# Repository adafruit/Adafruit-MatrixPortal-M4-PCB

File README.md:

## Adafruit MatrixPortal M4 - CircuitPython Powered Internet Display PCB

<a href="http://www.adafruit.com/products/4745"><br/>
Click here to purchase one from the Adafruit shop</a>

PCB files for the Adafruit MatrixPortal M4 - CircuitPython Powered Internet Display. 

Format is EagleCAD schematic and board layout
* https://www.adafruit.com/product/4745

### Description

Folks love our [wide selection of RGB matrices](https://www.adafruit.com/category/327) and accessories, for making custom colorful LED displays... and our RGB Matrix Shields and FeatherWings can be quickly soldered together to make the wiring much easier. But what if we made it even easier than that? **Like, no solder, no wiring, just instant plug-and-play?** Dream no more - with the **Adafruit Matrix Portal add-on for RGB Matrices**, there's never been an easier way to create powerful Internet-connected LED displays.

Plug directly into the back of [any HUB-75 compatible display (all the ones we stock will work) from 16x32 up to 64x64](https://www.adafruit.com/category/327)! Use the included screws to attach the power cable to the power plugs with a common screwdriver, then power it with any USB C power supply. (For larger projects, power the matrices with a separate 5V power adapter)

Then code up your project in [CircuitPython](https://learn.adafruit.com/rgb-led-matrices-matrix-panels-with-circuitpython) or [Arduino](https://learn.adafruit.com/adafruit-protomatter-rgb-matrix-library), our Protomatter matrix library works great on the SAMD51 chipset, knowing that you've got the wiring and level shifting all handled. Here's what you get:

 * **ATSAMD51J19 Cortex M4 processor**, 512KB flash, 192K of SRAM, with full Arduino or CircuitPython support
 * **ESP32 WiFi co-processor** with TLS support and SPI interface to the M4, with full Arduino or CircuitPython support
 * **USB Type C** connector for data and power connectivity
 * [**I2C STEMMA QT connector** for plug-n-play use of any of our STEMMA QT devices or sensors](https://www.adafruit.com/category/620) can also be used with [any Grove I2C devices using this adapter cable](https://www.adafruit.com/product/4528))
 * **JST 3-pin connector** that also has analog input/output, say for adding audio playback to projects
 * **LIS3DH accelerometer** for digital sand projects or detecting taps/orientation.
 * **GPIO breakouts** including 4 analog outputs with PWM and SPI support for adding other hardware.
 * **Address E line jumper** for use with 64x64 matrices (check your matrix to see which pin is used for address E!
 * **Two user interface buttons** + one reset button
 * **Indicator NeoPixel** and red LED
 * **Green power indicator LEDs** for both 3V and 5V power
 * **2x10 socket connector** fits snugly into 2x8 HUB75 ports without worrying about 'off by one' errors.

The Matrix Portal uses an ATMEL (Microchip) ATSAMD51J19, and an Espressif ESP32 Wi-Fi coprocessor with TLS/SSL support built-in. The M4 and ESP32 are a great couple - and each bring their own strengths to this board. The SAMD51 M4 has native USB so it can show up like a disk drive, act as a MIDI or HID keyboard/mouse, and of course bootload and debug over a serial port. It also has DACs, ADC, PWM, and tons of GPIO, so it can handle the high speed updating of the RGB matrix.

Meanwhile, the ESP32 has secure WiFi capabilities, and plenty of Flash and RAM to buffer sockets. By letting the ESP32 focus on the complex TLS/SSL computation and socket buffering, it frees up the SAMD51 to act as the user interface. You get a great programming experience thanks to the native USB with files available for drag-n-drop, and you don't have to spend a ton of processor time and memory to do SSL encryption/decryption and certificate management. It's the best of both worlds!

Comes with one fully-programmed and assembled MatrixPortal, preprogrammed with a rainbow digital sand demo for 32x64 LED matrices.

### License

Adafruit invests time and resources providing this open source design, please support Adafruit and open-source hardware by purchasing products from [Adafruit](https://www.adafruit.com)!

Designed by Limor Fried/Ladyada for Adafruit Industries.

Creative Commons Attribution/Share-Alike, all text above must be included in any redistribution. 
See license.txt for additional details.

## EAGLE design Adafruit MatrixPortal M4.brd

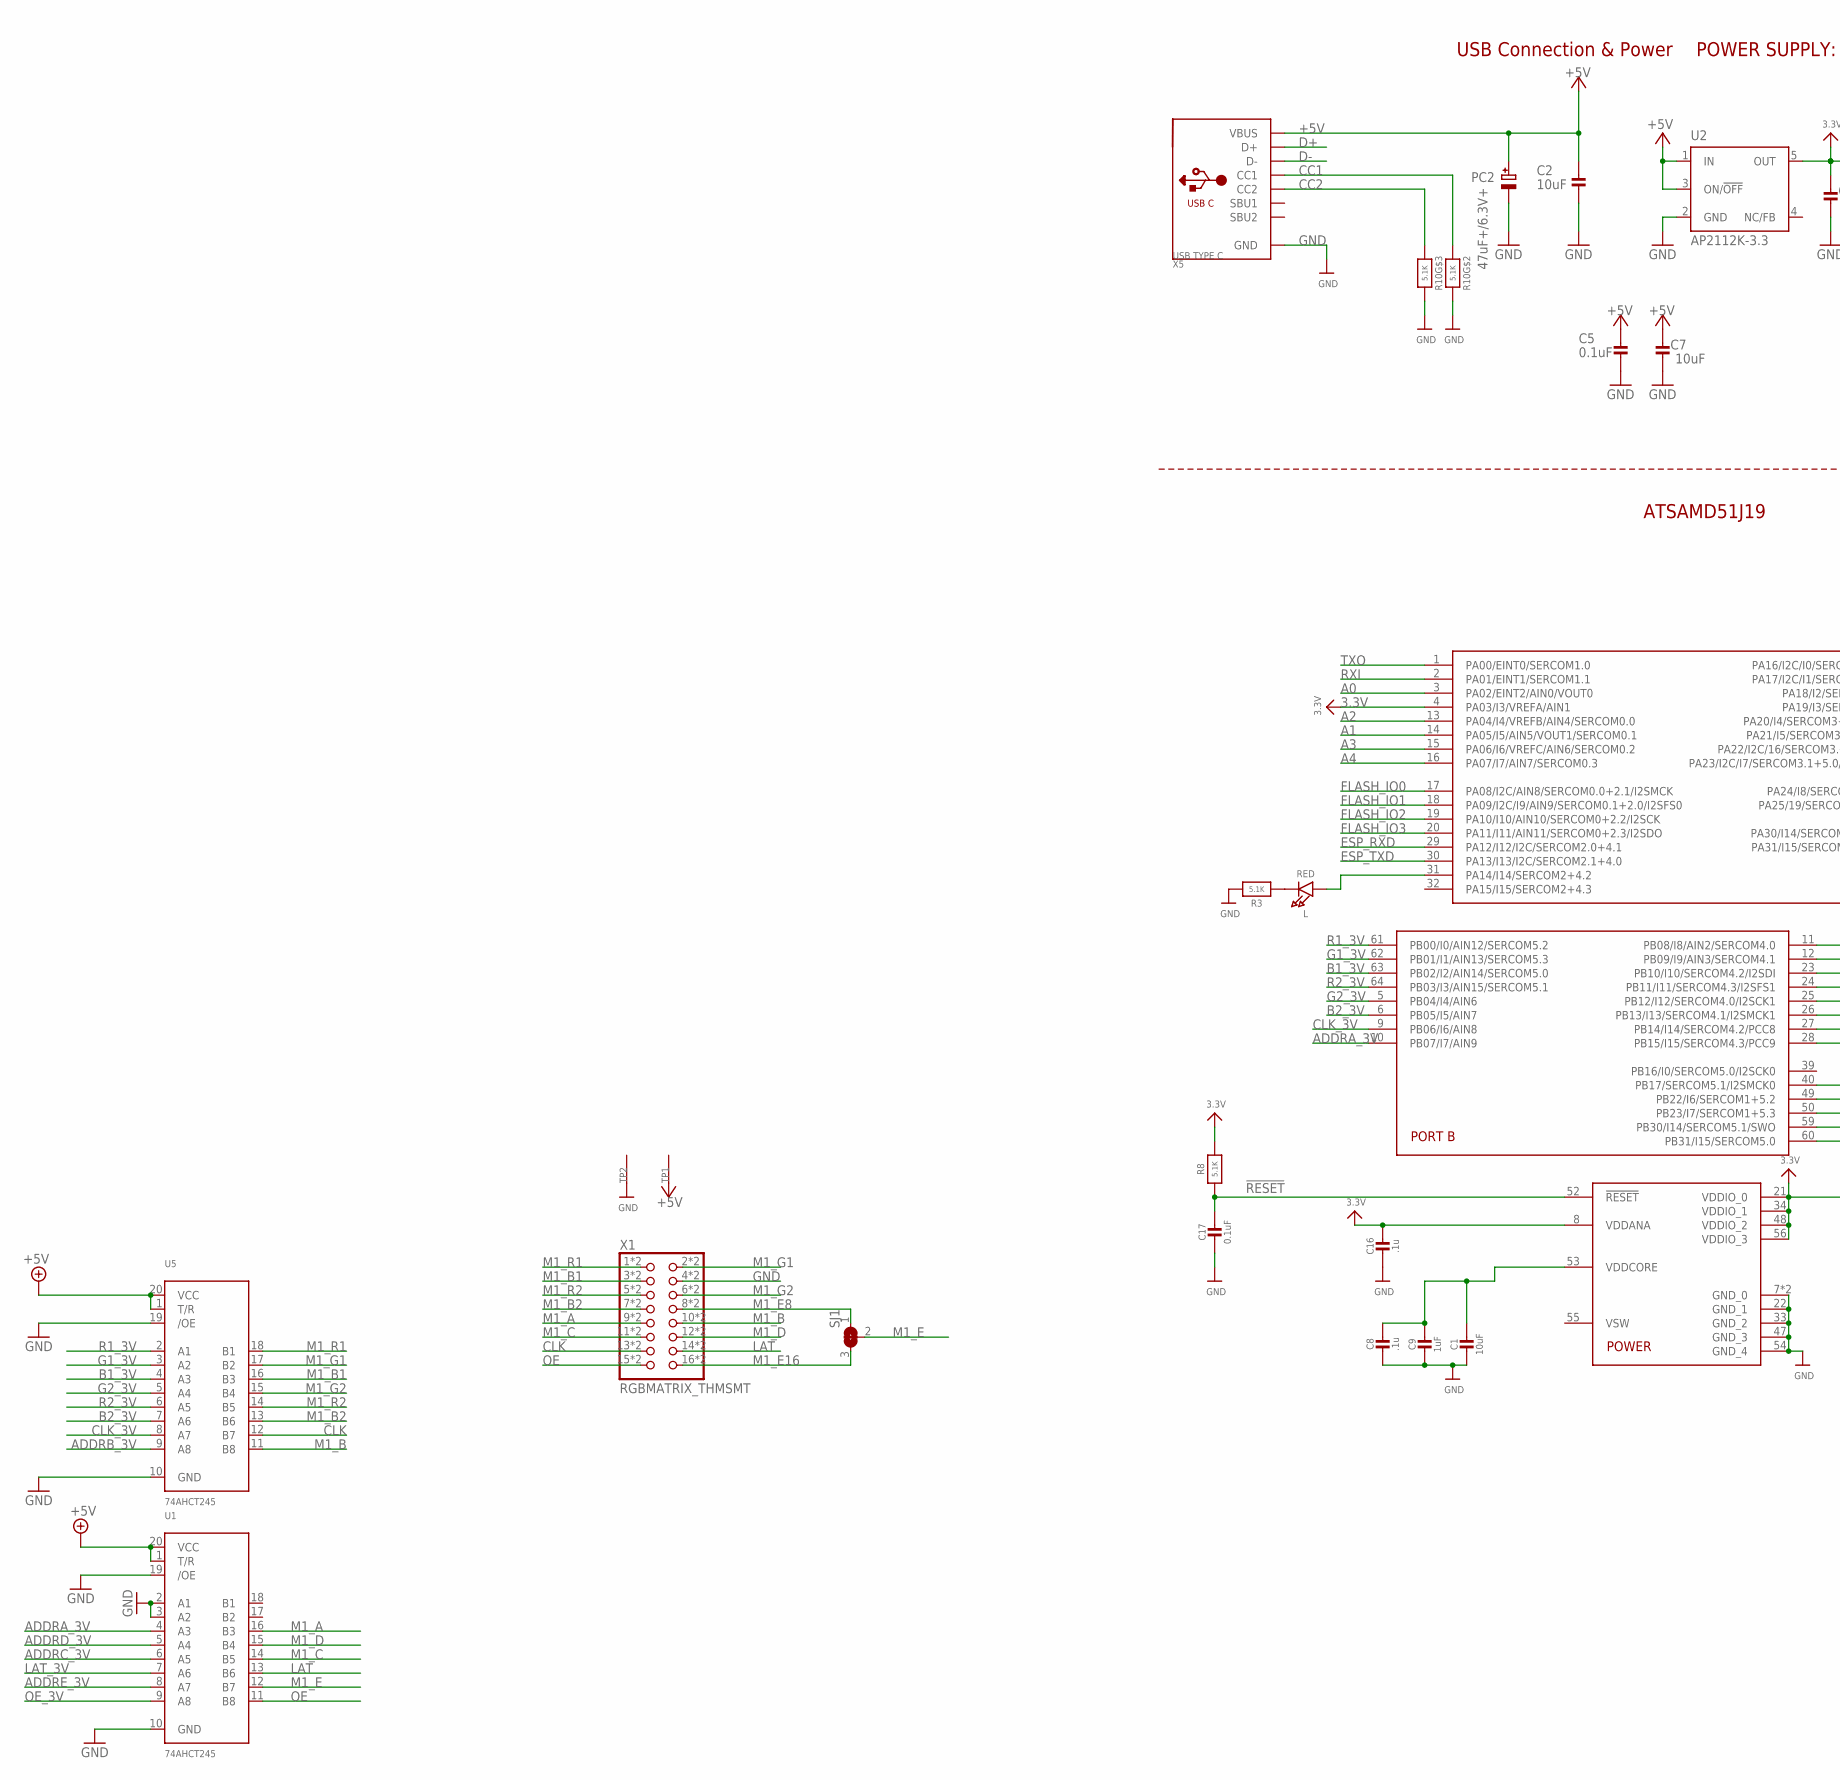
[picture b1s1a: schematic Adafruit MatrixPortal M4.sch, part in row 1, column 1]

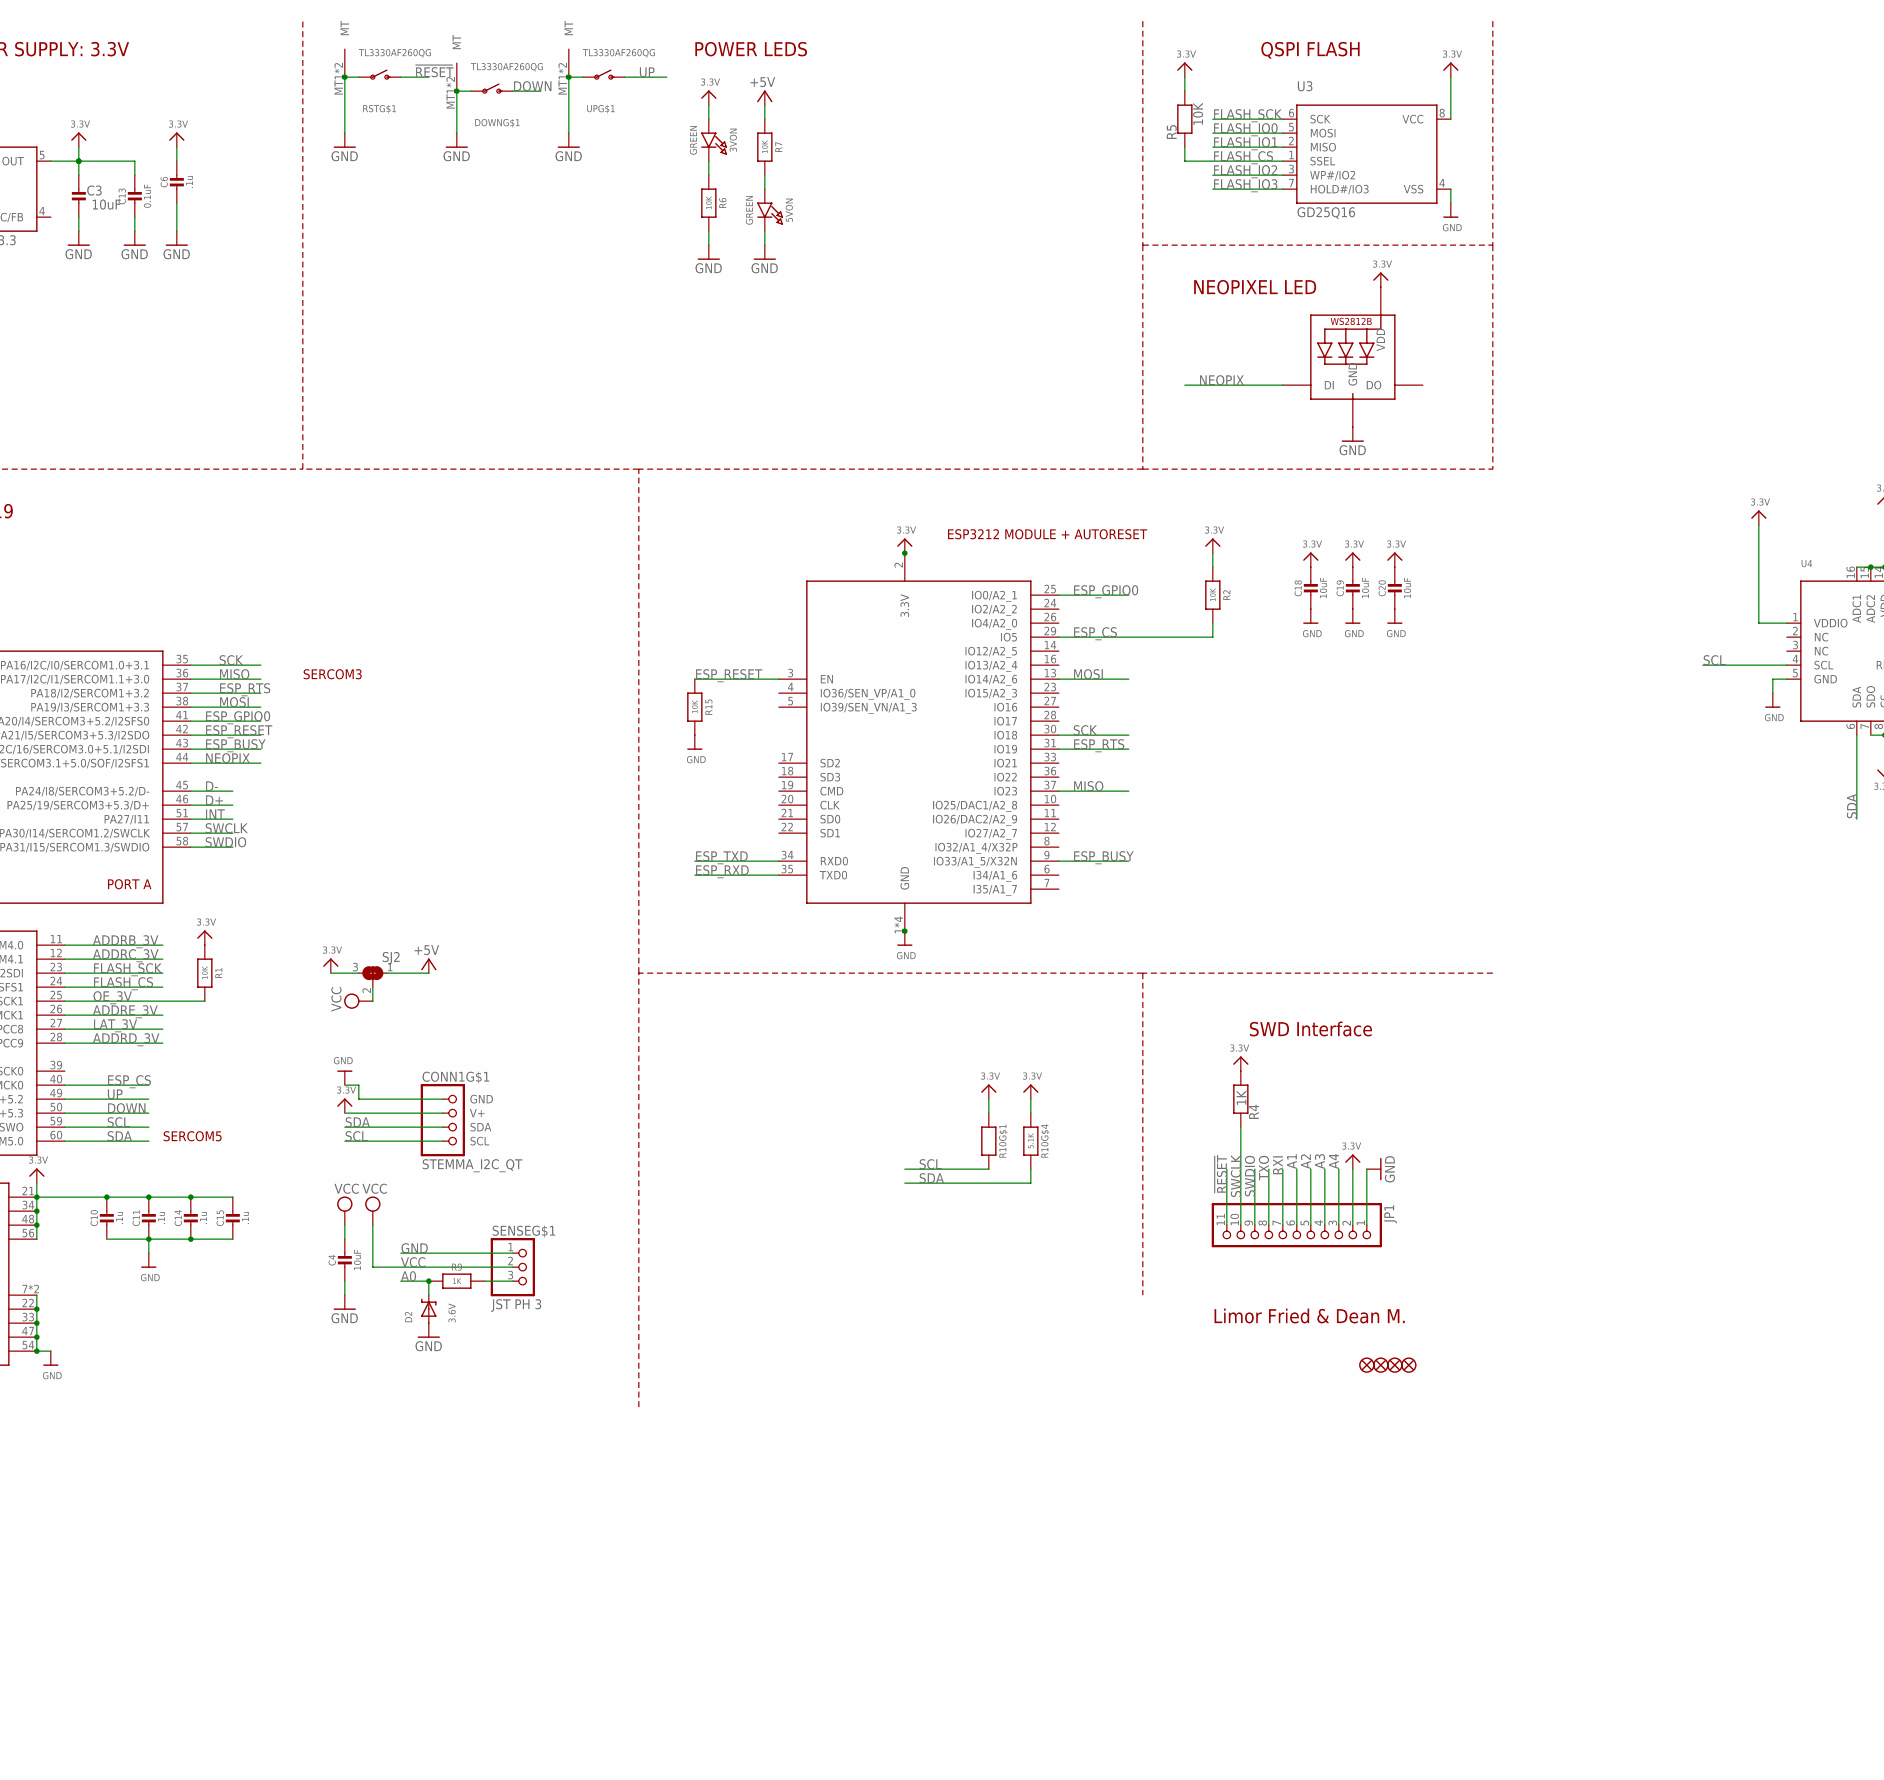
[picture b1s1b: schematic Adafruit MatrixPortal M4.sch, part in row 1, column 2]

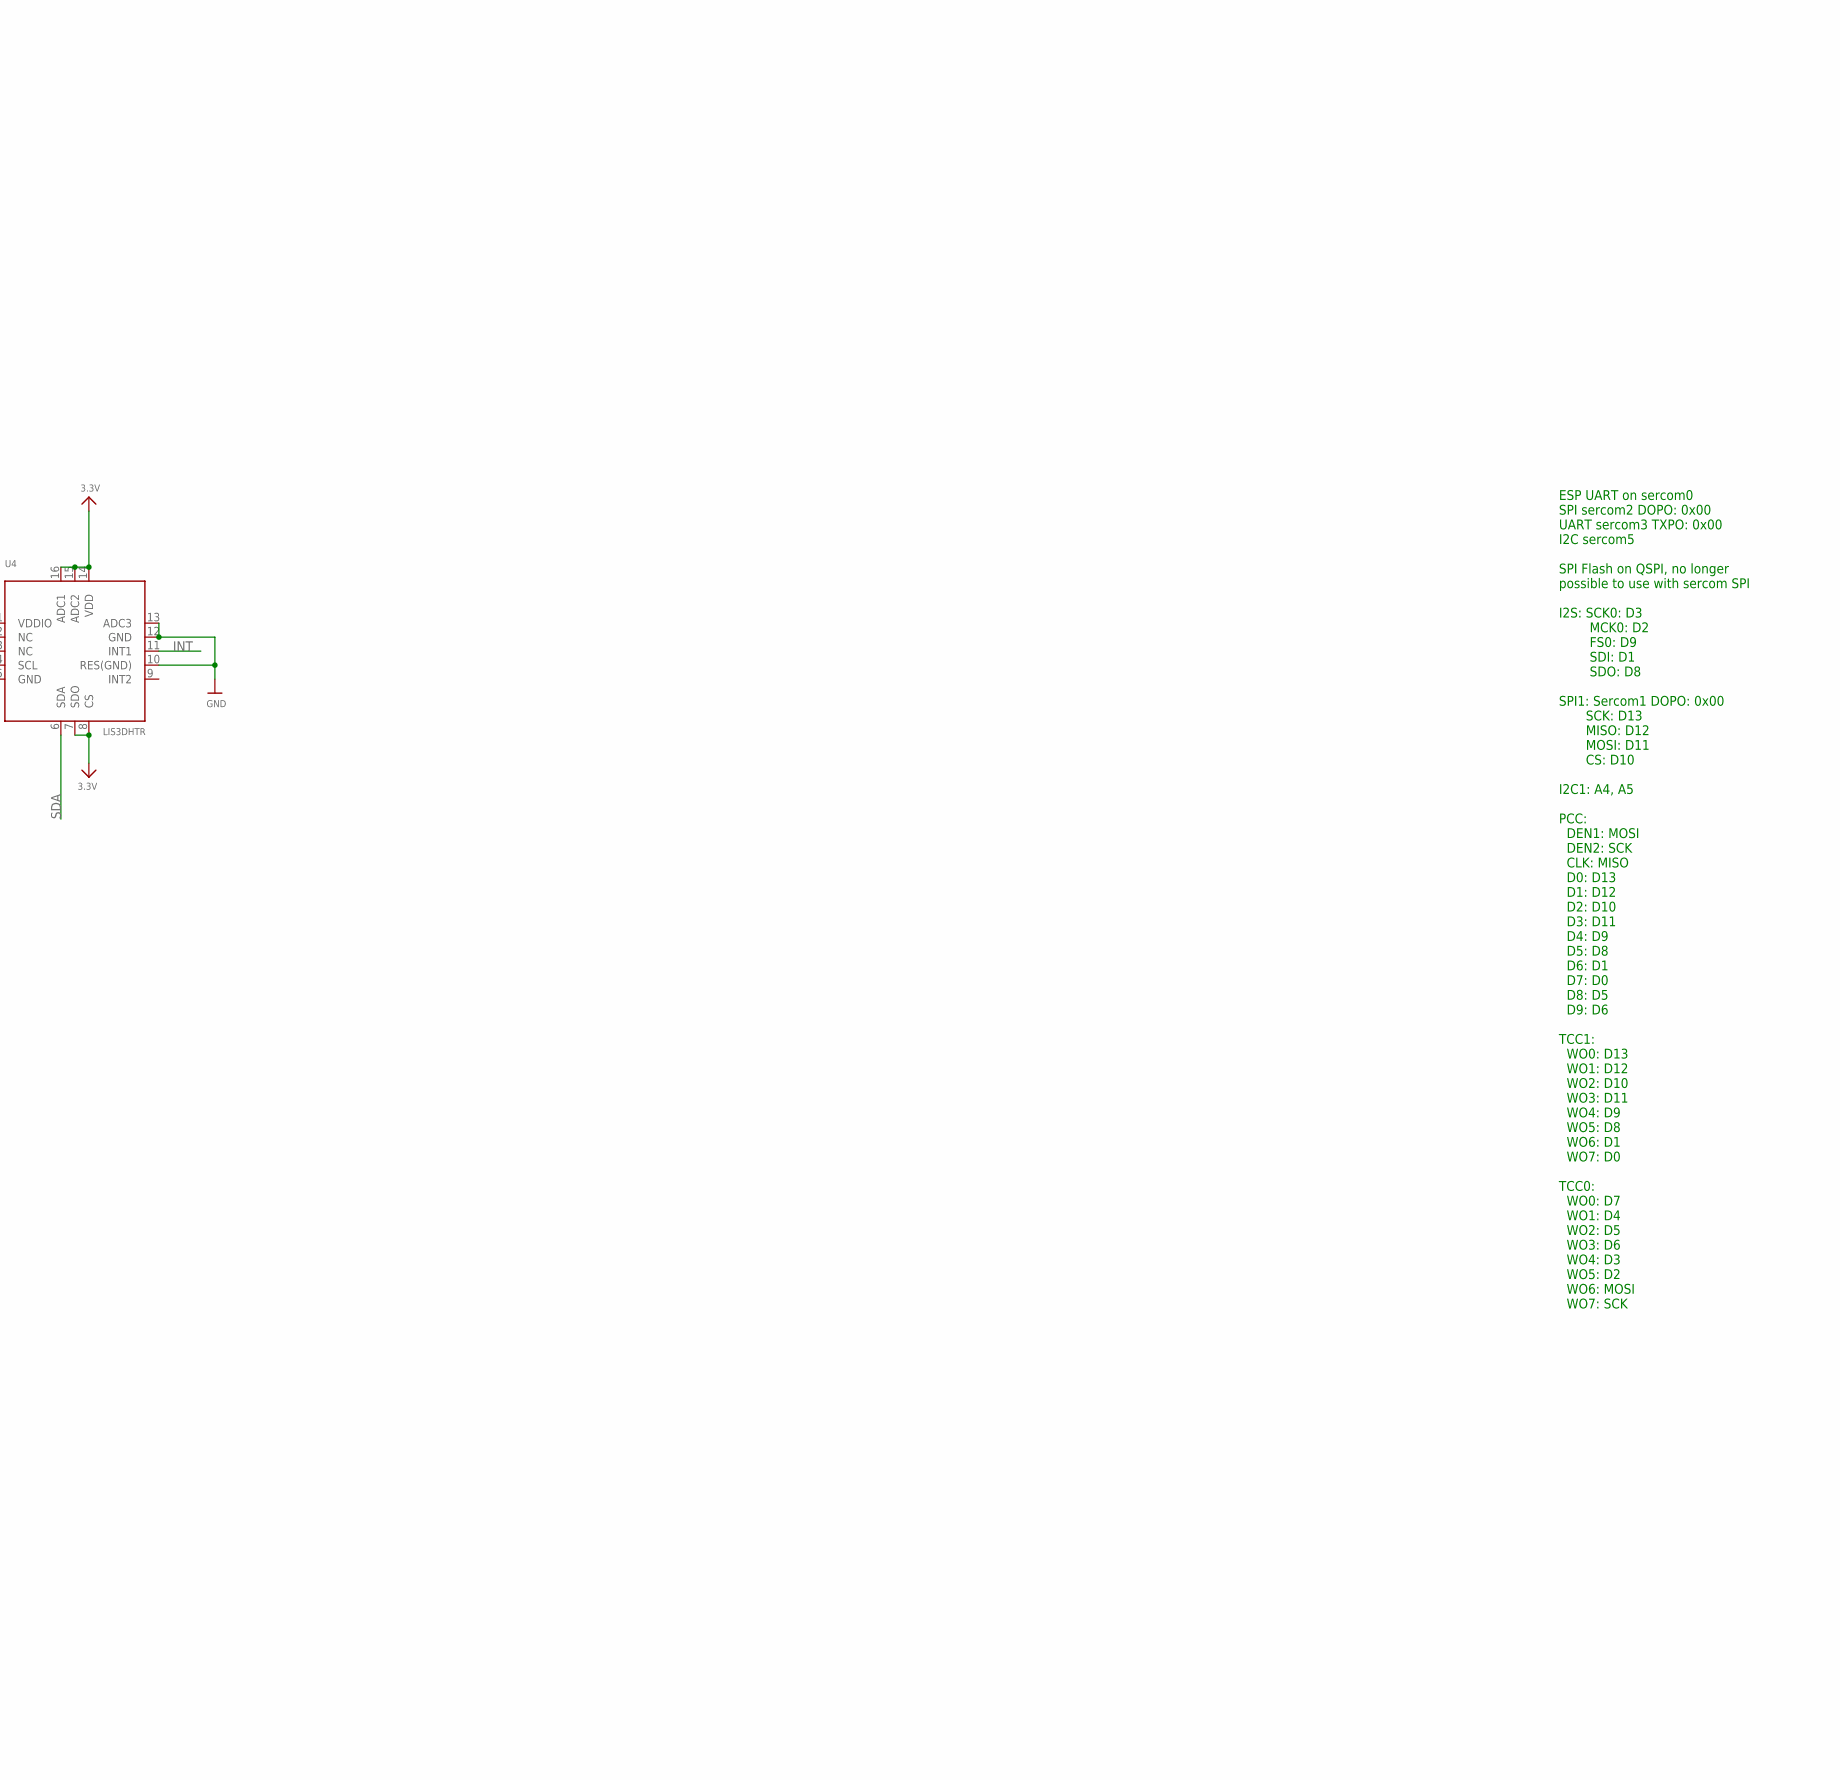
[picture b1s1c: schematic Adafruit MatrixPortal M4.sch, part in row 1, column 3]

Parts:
3VON, 5VON: GREEN; CHIPLED_0805_NOOUTLINE
C1, C2, C3, C4, C7, C18, C19, C20: 10uF; 0805-NO
C5, C13, C17: 0.1uF; 0603-NO
C6, C8, C10, C11, C14, C15, C16: .1u; 0603-NO
C9: 1uF; 0603-NO
CONN1: STEMMA_I2C_QT; JST_SH4
D2: 3.6V; SOD-323
DOWN: TL3330AF260QG; SPST_TACTILE_RA
FID1, FID2, FID3, FID4: FIDUCIAL_1MM
JP1: HEADER-1X11; 1X11_ROUND
L: RED; CHIPLED_0603_NOOUTLINE
LED1: WS2812B3535; LED3535
PC2: 47uF+/6.3V+; PANASONIC_D
R1, R2, R5, R6, R7, R15: 10K; 0603-NO
R3, R8: 5.1K; 0603-NO
R4, R9: 1K; 0603-NO
R10: 5.1K; RESPACK_4X0603
RST: TL3330AF260QG; SPST_TACTILE_RA
SENSE: JST PH 3; JSTPH3
SJ1, SJ2: SOLDERJUMPER_2WAY; SOLDERJUMPER_2WAY_OPEN_NOPASTE
TP1, TP2: SEWTAP_SMTNUTM3; SMT_NUT_3MM
U1, U5: 74AHCT245; TSSOP20
U2: AP2112K-3.3; SOT23-DBV
U3: GD25Q16; SOIC8_208MIL
U4: LIS3DHTR; LGA16_3X3MM
U$1: ATSAMD51J19; PQFN64-1
UP: TL3330AF260QG; SPST_TACTILE_RA
X1: RGBMATRIX_THMSMT; 2X08_SMTTHM_RGBMATRIX
X5: USB TYPE C; USB_C_CUSB31-CFM2AX-01-X
X6: ESP32_WROOM32; WROOM32

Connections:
3.3V: 3VON.A, C3.2, C6.2, C10.2, C11.2, C13.1, C14.2, C15.2, C16.2, C18.1, C19.1, C20.1, CONN1.2 (V+), JP1.2, LED1.2 (VDD), R1.1, R2.1, R4.2, R5.2, R8.2, R10.1, R10.4 (1), SJ2.3, U2.5 (OUT), U3.8 (VCC), U4.1 (VDDIO), U4.7 (SDO), U4.8 (CS), U4.14 (VDD), U4.15 (ADC2), U4.16 (ADC1), U$1.4 (PA03/I3/VREFA/AIN1), U$1.8 (VDDANA), U$1.21 (VDDIO_0), U$1.34 (VDDIO_1), U$1.48 (VDDIO_2), U$1.56 (VDDIO_3), X6.2 (3.3V)
!RESET: C17.2, JP1.11, R8.1, RST.2 (S), U$1.52 (!RESET)
+5V: C2.2, C5.2, C7.2, PC2.+, R7.1, SJ2.1, TP1.P$1, U1.1 (T/R), U1.20 (VCC), U2.1 (IN), U2.3 (ON/!OFF), U5.1 (T/R), U5.20 (VCC), X5.A4B9 (VBUS), X5.B4A9 (VBUS)
A0: D2.C, R9.2, U$1.3 (PA02/EINT2/AIN0/VOUT0)
A0_JST: R9.1, SENSE.3
A1: JP1.6, U$1.14 (PA05/I5/AIN5/VOUT1/SERCOM0.1)
A2: JP1.5, U$1.13 (PA04/I4/VREFB/AIN4/SERCOM0.0)
A3: JP1.4, U$1.15 (PA06/I6/VREFC/AIN6/SERCOM0.2)
A4: JP1.3, U$1.16 (PA07/I7/AIN7/SERCOM0.3)
ADDRA_3V: U1.4 (A3), U$1.10 (PB07/I7/AIN9)
ADDRB_3V: U5.9 (A8), U$1.11 (PB08/I8/AIN2/SERCOM4.0)
ADDRC_3V: U1.6 (A5), U$1.12 (PB09/I9/AIN3/SERCOM4.1)
ADDRD_3V: U1.5 (A4), U$1.28 (PB15/I15/SERCOM4.3/PCC9)
ADDRE_3V: U1.8 (A7), U$1.26 (PB13/I13/SERCOM4.1/I2SMCK1)
B1_3V: U5.4 (A3), U$1.63 (PB02/I2/AIN14/SERCOM5.0)
B2_3V: U5.7 (A6), U$1.6 (PB05/I5/AIN7)
CC1: R10.2 (1), X5.A5 (CC1)
CC2: R10.3 (1), X5.B5 (CC2)
CLK: U5.12 (B7), X1.13, X1.13S (13)
CLK_3V: U5.8 (A7), U$1.9 (PB06/I6/AIN8)
D+: U$1.46 (PA25/19/SERCOM3+5.3/D+), X5.A6 (D+), X5.B6 (D+)
D-: U$1.45 (PA24/I8/SERCOM3+5.2/D-), X5.A7 (D-), X5.B7 (D-)
DOWN: DOWN.2 (S), U$1.50 (PB23/I7/SERCOM1+5.3)
ESP_BUSY: U$1.43 (PA22/I2C/16/SERCOM3.0+5.1/I2SDI), X6.9 (IO33/A1_5/X32N)
ESP_CS: R2.2, U$1.40 (PB17/SERCOM5.1/I2SMCK0), X6.29 (IO5)
ESP_GPIO0: U$1.41 (PA20/I4/SERCOM3+5.2/I2SFS0), X6.25 (IO0/A2_1)
ESP_RESET: R15.1, U$1.42 (PA21/I5/SERCOM3+5.3/I2SDO), X6.3 (EN)
ESP_RTS: U$1.37 (PA18/I2/SERCOM1+3.2), X6.31 (IO19)
ESP_RXD: U$1.29 (PA12/I12/I2C/SERCOM2.0+4.1), X6.35 (TXD0)
ESP_TXD: U$1.30 (PA13/I13/I2C/SERCOM2.1+4.0), X6.34 (RXD0)
FLASH_CS: R5.1, U3.1 (SSEL), U$1.24 (PB11/I11/SERCOM4.3/I2SFS1)
FLASH_IO0: U3.5 (MOSI), U$1.17 (PA08/I2C/AIN8/SERCOM0.0+2.1/I2SMCK)
FLASH_IO1: U3.2 (MISO), U$1.18 (PA09/I2C/I9/AIN9/SERCOM0.1+2.0/I2SFS0)
FLASH_IO2: U3.3 (WP#/IO2), U$1.19 (PA10/I10/AIN10/SERCOM0+2.2/I2SCK)
FLASH_IO3: U3.7 (HOLD#/IO3), U$1.20 (PA11/I11/AIN11/SERCOM0+2.3/I2SDO)
FLASH_SCK: U3.6 (SCK), U$1.23 (PB10/I10/SERCOM4.2/I2SDI)
G1_3V: U5.3 (A2), U$1.62 (PB01/I1/AIN13/SERCOM5.3)
G2_3V: U5.5 (A4), U$1.5 (PB04/I4/AIN6)
GND: 5VON.C, C1.2, C2.1, C3.1, C4.2, C5.1, C6.1, C7.1, C8.1, C9.2, C10.1, C11.1, C13.2, C14.1, C15.1, C16.1, C17.1, C18.2, C19.2, C20.2, CONN1.1 (GND), D2.A, DOWN.1, DOWN.MT1 (MT), DOWN.MT2 (MT), JP1.1, LED1.4 (GND), PC2.-, R3.2, R6.2, R10.6 (2), R10.7 (2), R15.2, RST.1, RST.MT1 (MT), RST.MT2 (MT), SENSE.1, TP2.P$1, U1.2 (A1), U1.3 (A2), U1.10 (GND), U1.19 (/OE), U2.2 (GND), U3.4 (VSS), U4.5 (GND), U4.10 (RES(GND)), U4.12 (GND), U4.13 (ADC3), U5.10 (GND), U5.19 (/OE), U$1.7 (GND_0), U$1.22 (GND_1), U$1.33 (GND_2), U$1.47 (GND_3), U$1.54 (GND_4), U$1.EXP (GND_0), UP.1, UP.MT1 (MT), UP.MT2 (MT), X1.4, X1.4S (4), X5.A1B12 (GND), X5.B1A12 (GND), X6.1 (GND), X6.15 (GND), X6.38 (GND), X6.P$1 (GND)
INT: U4.11 (INT1), U$1.51 (PA27/I11)
LAT: U1.13 (B6), X1.14, X1.14S (14)
LAT_3V: U1.7 (A6), U$1.27 (PB14/I14/SERCOM4.2/PCC8)
M1_A: U1.16 (B3), X1.9, X1.9S (9)
M1_B: U5.11 (B8), X1.10, X1.10S (10)
M1_B1: U5.16 (B3), X1.3, X1.3S (3)
M1_B2: U5.13 (B6), X1.7, X1.7S (7)
M1_C: U1.14 (B5), X1.11, X1.11S (11)
M1_D: U1.15 (B4), X1.12, X1.12S (12)
M1_E: SJ1.2, U1.12 (B7)
M1_E8: SJ1.1, X1.8, X1.8S (8)
M1_E16: SJ1.3, X1.16, X1.16S (16)
M1_G1: U5.17 (B2), X1.2, X1.2S (2)
M1_G2: U5.15 (B4), X1.6, X1.6S (6)
M1_R1: U5.18 (B1), X1.1, X1.1S (1)
M1_R2: U5.14 (B5), X1.5, X1.5S (5)
MISO: U$1.36 (PA17/I2C/I1/SERCOM1.1+3.0), X6.37 (IO23)
MOSI: U$1.38 (PA19/I3/SERCOM1+3.3), X6.13 (IO14/A2_6)
unnamed: 5VON.A, R7.2
unnamed: 3VON.C, R6.1
unnamed: L.A, U$1.31 (PA14/I14/SERCOM2+4.2)
unnamed: L.C, R3.1
NEOPIX: LED1.1 (DI), U$1.44 (PA23/I2C/I7/SERCOM3.1+5.0/SOF/I2SFS1)
OE: U1.11 (B8), X1.15, X1.15S (15)
OE_3V: R1.2, U1.9 (A8), U$1.25 (PB12/I12/SERCOM4.0/I2SCK1)
R1_3V: U5.2 (A1), U$1.61 (PB00/I0/AIN12/SERCOM5.2)
R2_3V: U5.6 (A5), U$1.64 (PB03/I3/AIN15/SERCOM5.1)
RXI: JP1.7, U$1.2 (PA01/EINT1/SERCOM1.1)
SCK: U$1.35 (PA16/I2C/I0/SERCOM1.0+3.1), X6.30 (IO18)
SCL: CONN1.4 (SCL), R10.8 (2), U4.4 (SCL), U$1.59 (PB30/I14/SERCOM5.1/SWO)
SDA: CONN1.3 (SDA), R10.5 (2), U4.6 (SDA), U$1.60 (PB31/I15/SERCOM5.0)
SWCLK: JP1.10, R4.1, U$1.57 (PA30/I14/SERCOM1.2/SWCLK)
SWDIO: JP1.9, U$1.58 (PA31/I15/SERCOM1.3/SWDIO)
TXO: JP1.8, U$1.1 (PA00/EINT0/SERCOM1.0)
UP: U$1.49 (PB22/I6/SERCOM1+5.2), UP.2 (S)
VCC: C4.1, SENSE.2, SJ2.2
VDDCORE: C1.1, C8.2, C9.1, U$1.53 (VDDCORE)

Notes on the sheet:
Limor Fried & Dean M.
USB Connection & Power
POWER SUPPLY: 3.3V
POWER LEDS
ATSAMD51J19
NEOPIXEL LED
QSPI FLASH
SWD Interface
ESP UART on sercom0 SPI sercom2 DOPO: 0x00 UART sercom3 TXPO: 0x00 I2C sercom5 SPI Flash on QSPI, no longer possible to use with sercom SPI I2S: SCK0: D3 MCK0: D2 FS0: D9 SDI: D1 SDO: D8 SPI1: Sercom1 DOPO: 0x00 SCK: D13 MISO: D12 MOSI: D11 CS: D10 I2C1: A4, A5 PCC: DEN1: MOSI DEN2: SCK CLK: MISO D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
ESP3212 MODULE + AUTORESET
SERCOM5
SERCOM3

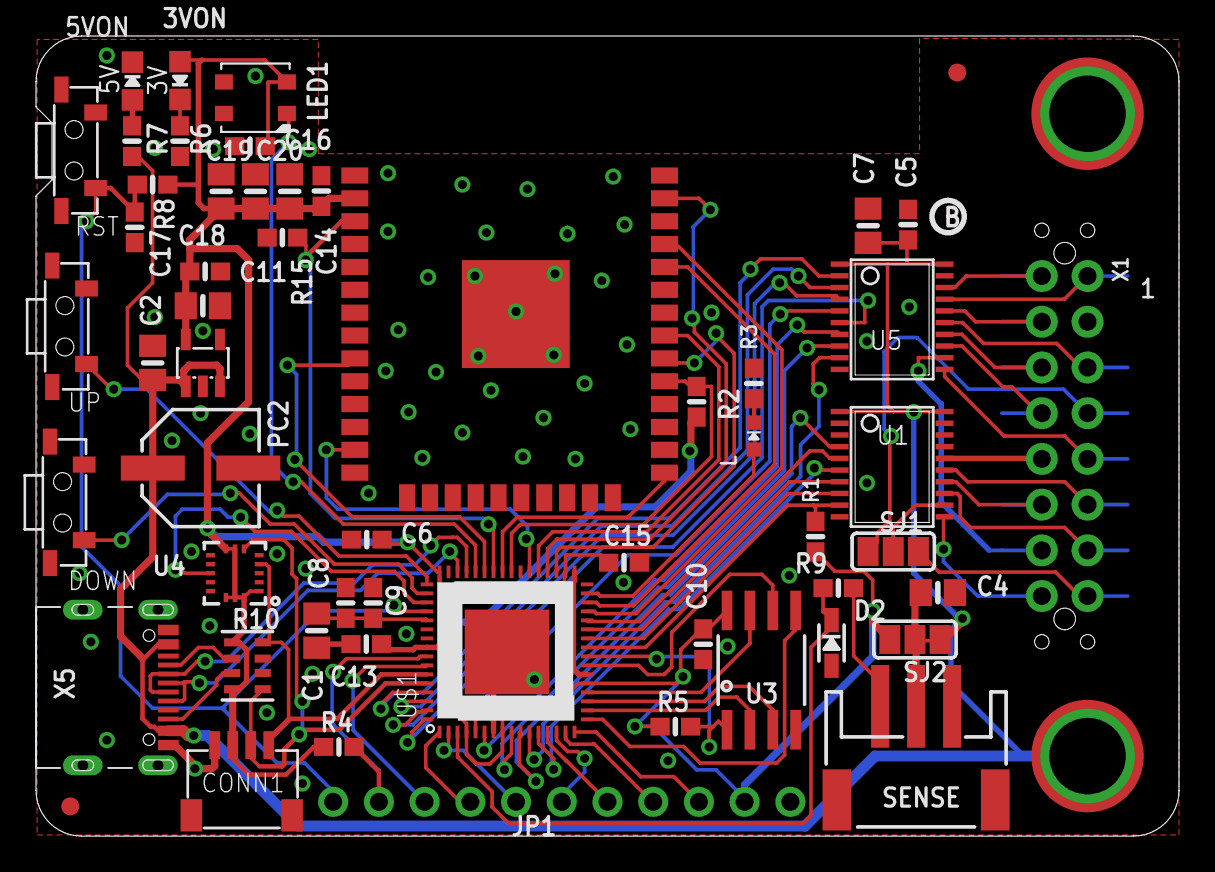
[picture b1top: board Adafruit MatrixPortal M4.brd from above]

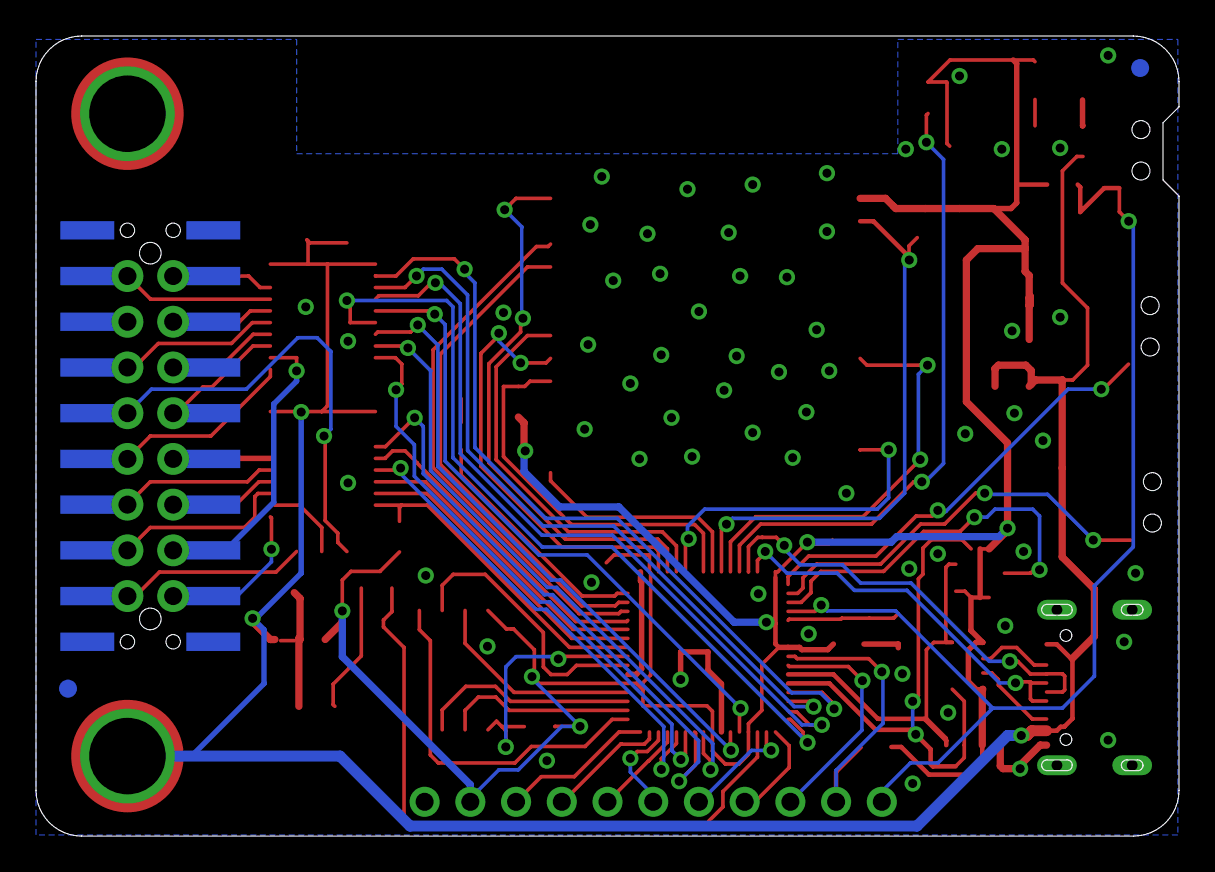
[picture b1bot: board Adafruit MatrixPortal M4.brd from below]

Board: 2 copper layers, 63.5 x 44.5 mm, 62 parts (3 on the bottom side), 76 nets.

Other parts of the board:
U$41: MATRIXPORTAL_BOT
U$44: PCBFEAT-REV-040
U$45: MATRIXPORTAL_TOP

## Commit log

2020-09-25 Added board and schematic files and template
2020-09-25 Updated dimensions
2020-09-25 Cleaned up MatrixPortal Schematic
2022-05-20 Added PrettyPins
2024-10-10 Fix MTX_ADDR* pinout in .pdf

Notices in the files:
parts and their libraries:
microbuilder: This work is placed in the public domain, and may be freely used for commercial and non-commercial work with the following conditions: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
SparkFun-Aesthetics: Licensing: CC v3.0 Share-Alike You are welcome to use this library for commercial purposes.
